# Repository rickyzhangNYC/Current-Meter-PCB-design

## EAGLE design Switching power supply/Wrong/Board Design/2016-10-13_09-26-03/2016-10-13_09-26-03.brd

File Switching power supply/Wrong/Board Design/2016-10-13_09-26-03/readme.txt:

**********************************************************
*************  Important Instructions Follow  ************
**********************************************************

All files exported to: Z:\\48\\19\\4819765\\1\Eagle\2016-10-13_09-26-03\2016-10-13_09-26-03.xml

**********************************************************
*****************Schematic Instructions  *******************
**********************************************************

To import your new Schematic file into Eagle:

1. Unzip the downloaded folder files to local directory and Start Eagle.
2. Select "File"->"Open"->"Schematic..." from the menu at the top of
the screen.
3. Browse to your newly exported file and select the ".sch" file extension.
4. You should now see your schamtic available in Eagle.

**********************************************************
*******************  PCB Instructions  *******************
**********************************************************

To import your new BOARD file into Eagle:

1. Unzip the downloaded folder files to local directory and Start Eagle.
2. Select "File"->"Open"->"Board..." from the menu at the top of
the screen.
3. Browse to your newly exported file and select the ".brd" file extension.
4. Planes will need to be repoured to update the polygon fills
	1. Once your board is loaded and before the repour, the default design rule
	   should be updated for Mask and thermal relief.
		a. Goto Edit and select Design Rules.
			-Select Masks Tab; Set Stop (Min & Max) to 0.0mm
			-Select Supply Tab; Set Thermal Isolation to 0.0mm
	2. To pour the polygon fills, goto Tools and select Ratsnest
	3. The polygons should all be filled now.
5. You should now have an image of your board available in Eagle.

**********************************************************
*******************  LIB Instructions  *******************
**********************************************************

To import your new library into Eagle:

1. Start Eagle.
2. Select "File"->"New"->"Library" from the menu.
3. In the blank library window, select "File" -> "Execute Script"
from the menu.
5. Browse to your newly exported Eagle Script file (".scr" file extension)
6. After opening the file, the script will populate the new library.
Layer 93 should NOT exist.
7. Use "File"->"Save" (or "Save As..") to save the library to the desired
location in Eagle native format.

For additional information, please visit this site:
http://www.accelerated-designs.com/help/Eagle_import.html

You may also find this video helpful:
http://youtu.be/5jGuWY-Yy3Q

**********************************************************
**********************************************************
**********************************************************

Padstack "C1009060090600000P00148P00000" renamed to "C100906009060000"
Component "TPS63051YFFR" renamed to "TPS63051YFFR"
Component "LMK107BBJ106MAHT" renamed to "LMK107BBJ106MAHT"
Component "CL10A106MQ8NNNC" renamed to "CL10A106MQ8NNNC"
Component "CRCW0402100KFKED" renamed to "CRCW0402100KFKED"
Component "CRCW0603100KFKEA" renamed to "CRCW0603100KFKEA"
Component "LQM2HPN1R5MG0L" renamed to "LQM2HPN1R5MG0L"
Component "GRM155R61A102KA01D" renamed to "GRM155R61A102KA01D"
Component "TP-1502" renamed to "TP-1502"

Ultra Librarian Gold 8.1.44 Process Report

Message - Padstack "RX26Y38D0T" Shape(4) is a CIRCLE with no diameter.
Message - Padstack "C100906009060000" Shape(4) is a CIRCLE with no diameter.
Message - Padstack "RX22Y24D0T" Shape(4) is a CIRCLE with no diameter.
Message - Padstack "RX46Y87D0T" Shape(4) is a CIRCLE with no diameter.
Message - Component "TPS63051YFFR" attribute "Datasheet URL" references text style "" that is not in the database.
The default pattern text style "H50s3" was substituted.
Message - Component "TPS63051YFFR" attribute "Frequency" references text style "" that is not in the database.
The default pattern text style "H50s3" was substituted.
Message - Component "TPS63051YFFR" attribute "Imax" references text style "" that is not in the database.
The default pattern text style "H50s3" was substituted.
Message - Component "TPS63051YFFR" attribute "Package" references text style "" that is not in the database.
The default pattern text style "H50s3" was substituted.
Message - Component "TPS63051YFFR" attribute "Mktg_Package" references text style "" that is not in the database.
The default pattern text style "H50s3" was substituted.
Message - Component "TPS63051YFFR" attribute "NSID" references text style "" that is not in the database.
The default pattern text style "H50s3" was substituted.
Message - Component "CRCW0402100KFKED" attribute "Resistance" references text style "" that is not in the database.
The default pattern text style "H50s3" was substituted.
Message - Component "CRCW0402100KFKED" attribute "Power" references text style "" that is not in the database.
The default pattern text style "H50s3" was substituted.
Message - Component "CRCW0402100KFKED" attribute "Tolerance" references text style "" that is not in the database.
The default pattern text style "H50s3" was substituted.
Message - Component "CRCW0603100KFKEA" attribute "Resistance" references text style "" that is not in the database.
The default pattern text style "H50s3" was substituted.
Message - Component "CRCW0603100KFKEA" attribute "Power" references text style "" that is not in the database.
The default pattern text style "H50s3" was substituted.
Message - Component "CRCW0603100KFKEA" attribute "Tolerance" references text style "" that is not in the database.
The default pattern text style "H50s3" was substituted.
Message - Component "LQM2HPN1R5MG0L" attribute "L" references text style "" that is not in the database.
The default pattern text style "H50s3" was substituted.
Message - Component "LQM2HPN1R5MG0L" attribute "DCR" references text style "" that is not in the database.
The default pattern text style "H50s3" was substituted.
Message - Component "LQM2HPN1R5MG0L" attribute "IDC" references text style "" that is not in the database.
The default pattern text style "H50s3" was substituted.
Message - Component "GRM155R61A102KA01D" attribute "Cap" references text style "" that is not in the database.
The default pattern text style "H50s3" was substituted.
Message - Component "GRM155R61A102KA01D" attribute "ESR" references text style "" that is not in the database.
The default pattern text style "H50s3" was substituted.
Message - Component "GRM155R61A102KA01D" attribute "IRMS" references text style "" that is not in the database.
The default pattern text style "H50s3" was substituted.
Message - Component "GRM155R61A102KA01D" attribute "VDC" references text style "" that is not in the database.
The default pattern text style "H50s3" was substituted.

TextStyle count:  24
Padstack count:   8
Pattern count:    5
Symbol count:     5
Component count:  8

Export

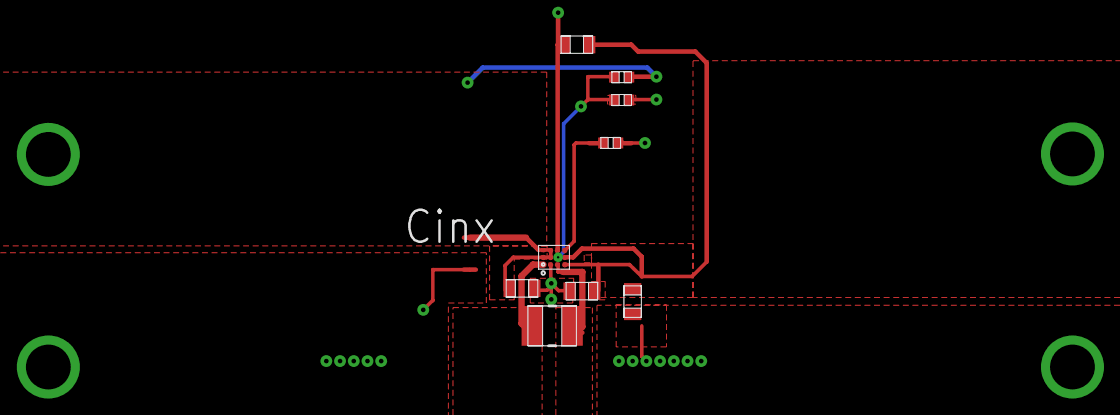
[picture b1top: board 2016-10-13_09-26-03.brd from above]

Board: 4 copper layers, 13 parts (0 on the bottom side), 7 nets.

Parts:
Cin: 0603
Cout: 0603
Coutx: 0603
Css: 0402
GND1, GND2: TP-1502
L1: 1008
Rpfm: 0402
Rpg: 0603
Rpwm: 0402
U1: YFF0012AFAF
VIN: TP-1502
VOUT: TP-1502

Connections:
0: Cin.2, Cout.2, Coutx.2, Css.2, GND1.1, GND2.1, Rpfm.1, Rpfm.2, Rpwm.2, U1.4, U1.8
2: Cin.1, Rpwm.1, U1.2, U1.3, U1.5, U1.6, VIN.1
3: Css.1, U1.12
4: Cout.1, Coutx.1, Rpg.1, U1.10, U1.11, VOUT.1
5: L1.1, U1.1
6: L1.2, U1.7
8: Rpg.2, U1.9
